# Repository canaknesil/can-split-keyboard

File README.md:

# Can Split Keyboard

Note: THIS KEYBOARD IS NOT READY FOR MANUFACTURING !!!

PCB design for split ortholinear keyboard with 7x6 keys on both sides. 

Can Split Keyboard is based on [Split
Infinitive](https://github.com/peej/for-split-keyboard).

The main differences are
* 7x6 keys on both sides (rather than 6x5) to enable a more complete
  key set. 
* Arduino Nano (rather than Pro Micro).

Inherited features:
* Designed to be easy to build with minimal soldering experience.
* Switch plate cutouts in the PCB so the same PCB can also be used as a switch plate.
* Serial communication over a TRRS cable in split configuration.
* Single PCB design for both keyboard sides.

## Bill of Materials (BOM)

* 4 PCBs, 2 for components and 2 as switch plates.
* 84 MX compatible switches.
* 84 1n4148 diodes.
* 2 Arduino Nano controllers with headers or DIP sockets.
* 2 PJ320A 3.5mm TRRS jacks.
* TRRS cable and micro USB cable.
* 84 MX compatible key caps.

### Tools

* Hacksaw blade or similar
* Flat edged file or sanding paper
* Soldering iron and solder

When uploading the gerber files to the manufacturer, use the default
PCB settings. The plate PCB thickness should be 1.6mm for the switches
to snap into the plate securely. 

## Construction

* You will need 4 PCBs.
* Use a hacksaw blade to remove the cutouts for the switch plate PCBs.
* Solder the diodes onto the underside of each PCB.
* Solder on the Arduino Nano headers (or DIP socket) onto the
  underside of each PCB, do not solder on the Arduino Nano yet.
* Solder the PJ320A TRRS sockets onto the underside of each PCB.
  * There are 2 positions per board, use the right position on the left hand PCB and the left position on the right hand PCB.
  * Ensure that the pins will not foul the placement of the switches and still allow the switches to sit flat on the PCB.
  * You may need to slightly bend the pins inwards away from the switch footprint.
* Insert the switches into the plate and then into the top of the PCBs.
  * Insert all the switches and ensure that the pins of each switch are correctly coming through the board and are not bent under the PCB.
* Solder all the switch pins.
* Solder on the Arduino Nano, ensure that you get them the correct way around, the chip side should be face down towards the PCB.
* Connect the halves together with the TRRS cable.
* Flash both Arduino Nanos with the firmware, see the [QMK documentation](http://qmk.fm/) on how to build and flash the firmware.

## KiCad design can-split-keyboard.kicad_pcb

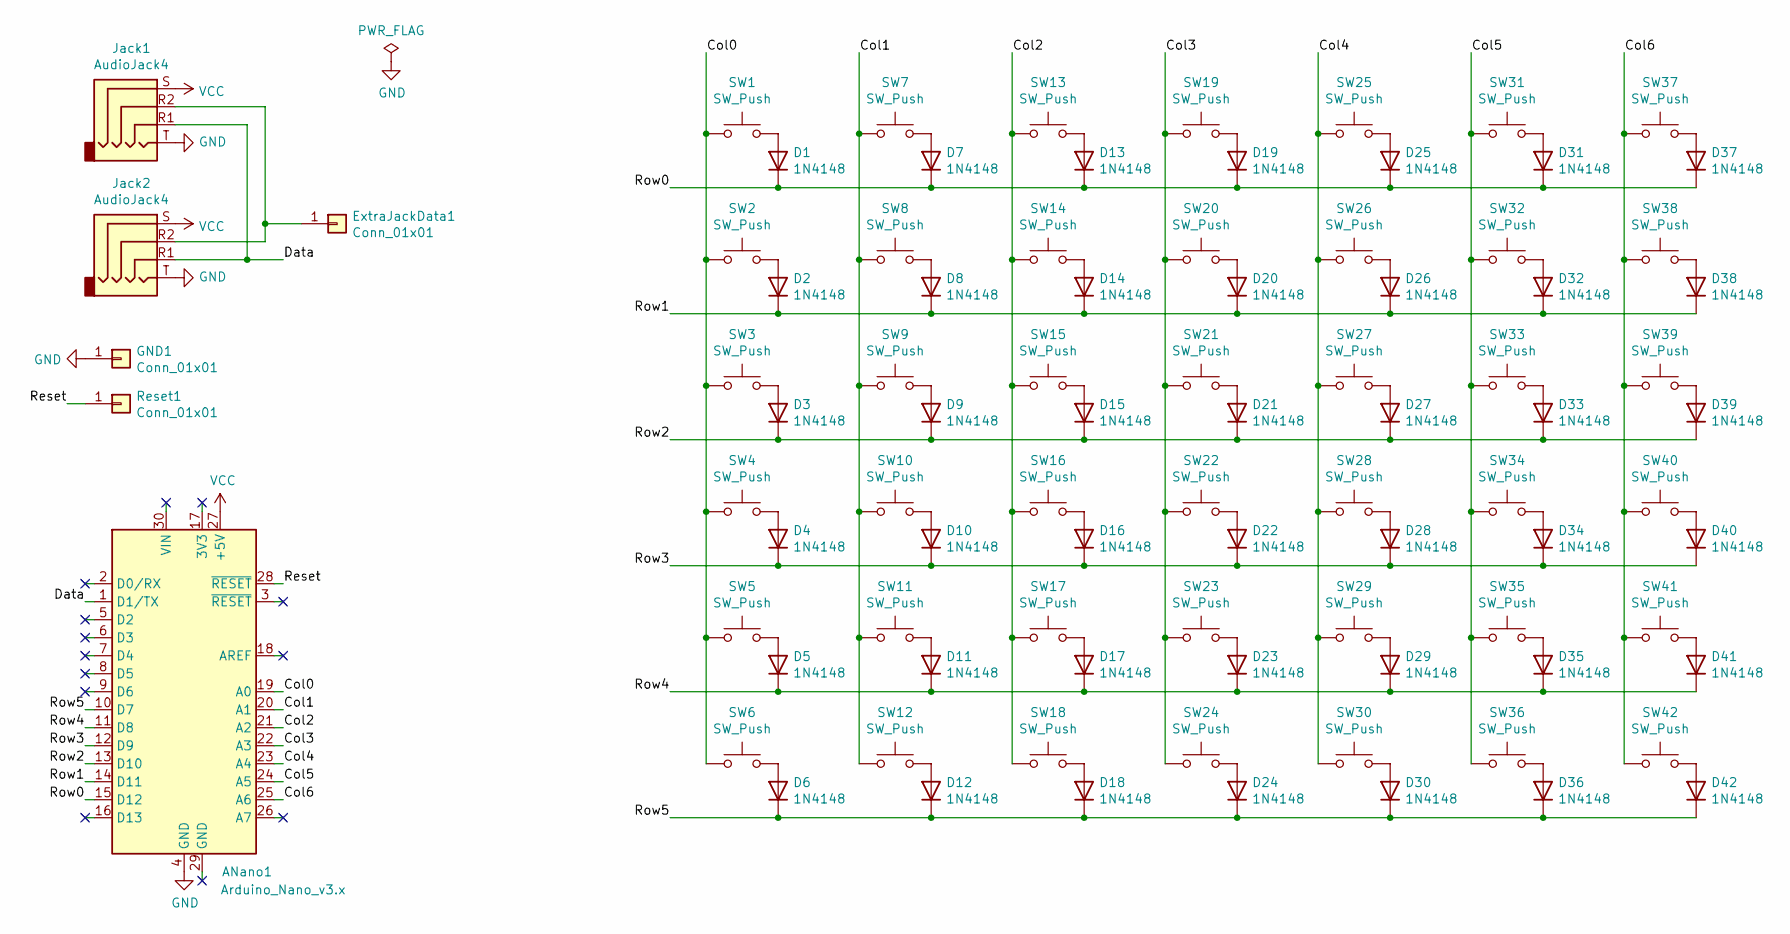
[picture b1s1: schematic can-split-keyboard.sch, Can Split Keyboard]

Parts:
ANano1: Arduino_Nano_v3.x; Arduino_Nano
D1, D2, D3, D4, D5, D6, D7, D8, D9, D10, D11, D12, D13, D14, D15, D16, D17, D18, D19, D20, D21, D22, D23, D24, D25, D26, D27, D28, D29, D30, D31, D32, D33, D34, D35, D36, D37, D38, D39, D40, D41, D42: 1N4148; D_DO-35_SOD27_P7.62mm_Horizontal
ExtraJackData1: Conn_01x01; Single_Pad
GND1: Conn_01x01; Square_Pad
Jack1, Jack2: AudioJack4; PJ-320A
Reset1: Conn_01x01; Square_Pad
SW1, SW2, SW3, SW4, SW5, SW7, SW8, SW9, SW10, SW11, SW13, SW14, SW15, SW16, SW17, SW18, SW19, SW20, SW21, SW22, SW23, SW24, SW25, SW26, SW27, SW28, SW29, SW30, SW31, SW32, SW33, SW34, SW35, SW37, SW38, SW39, SW40, SW41: SW_Push; MX_CUTOUT
SW6, SW36: SW_Push; MX2U_CUTOUT
SW12, SW42: SW_Push; MX

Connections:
/Col0: ANano1.19 (A0), SW1.1, SW2.1, SW3.1, SW4.1, SW5.1, SW6.1
/Col1: ANano1.20 (A1), SW7.1, SW8.1, SW9.1, SW10.1, SW11.1, SW12.1
/Col2: ANano1.21 (A2), SW13.1, SW14.1, SW15.1, SW16.1, SW17.1, SW18.1
/Col3: ANano1.22 (A3), SW19.1, SW20.1, SW21.1, SW22.1, SW23.1, SW24.1
/Col4: ANano1.23 (A4), SW25.1, SW26.1, SW27.1, SW28.1, SW29.1, SW30.1
/Col5: ANano1.24 (A5), SW31.1, SW32.1, SW33.1, SW34.1, SW35.1, SW36.1
/Col6: ANano1.25 (A6), SW37.1, SW38.1, SW39.1, SW40.1, SW41.1, SW42.1
/Data: ANano1.1 (D1/TX), Jack1.R1, Jack2.R1
/Reset: ANano1.28 (~RESET), Reset1.1
/Row0: ANano1.15 (D12), D1.1 (K), D7.1 (K), D13.1 (K), D19.1 (K), D25.1 (K), D31.1 (K), D37.1 (K)
/Row1: ANano1.14 (D11), D2.1 (K), D8.1 (K), D14.1 (K), D20.1 (K), D26.1 (K), D32.1 (K), D38.1 (K)
/Row2: ANano1.13 (D10), D3.1 (K), D9.1 (K), D15.1 (K), D21.1 (K), D27.1 (K), D33.1 (K), D39.1 (K)
/Row3: ANano1.12 (D9), D4.1 (K), D10.1 (K), D16.1 (K), D22.1 (K), D28.1 (K), D34.1 (K), D40.1 (K)
/Row4: ANano1.11 (D8), D5.1 (K), D11.1 (K), D17.1 (K), D23.1 (K), D29.1 (K), D35.1 (K), D41.1 (K)
/Row5: ANano1.10 (D7), D6.1 (K), D12.1 (K), D18.1 (K), D24.1 (K), D30.1 (K), D36.1 (K), D42.1 (K)
GND: ANano1.4 (GND), GND1.1, Jack1.T, Jack2.T
unnamed: D1.2 (A), SW1.2
unnamed: D2.2 (A), SW2.2
unnamed: D3.2 (A), SW3.2
unnamed: D4.2 (A), SW4.2
unnamed: D5.2 (A), SW5.2
unnamed: D6.2 (A), SW6.2
unnamed: D7.2 (A), SW7.2
unnamed: D8.2 (A), SW8.2
unnamed: D9.2 (A), SW9.2
unnamed: D10.2 (A), SW10.2
unnamed: D11.2 (A), SW11.2
unnamed: D12.2 (A), SW12.2
unnamed: D13.2 (A), SW13.2
unnamed: D14.2 (A), SW14.2
unnamed: D15.2 (A), SW15.2
unnamed: D16.2 (A), SW16.2
unnamed: D17.2 (A), SW17.2
unnamed: D18.2 (A), SW18.2
unnamed: D19.2 (A), SW19.2
unnamed: D20.2 (A), SW20.2
unnamed: D21.2 (A), SW21.2
unnamed: D22.2 (A), SW22.2
unnamed: D23.2 (A), SW23.2
unnamed: D24.2 (A), SW24.2
unnamed: D25.2 (A), SW25.2
unnamed: D26.2 (A), SW26.2
unnamed: D27.2 (A), SW27.2
unnamed: D28.2 (A), SW28.2
unnamed: D29.2 (A), SW29.2
unnamed: D30.2 (A), SW30.2
unnamed: D31.2 (A), SW31.2
unnamed: D32.2 (A), SW32.2
unnamed: D33.2 (A), SW33.2
unnamed: D34.2 (A), SW34.2
unnamed: D35.2 (A), SW35.2
unnamed: D36.2 (A), SW36.2
unnamed: D37.2 (A), SW37.2
unnamed: D38.2 (A), SW38.2
unnamed: D39.2 (A), SW39.2
unnamed: D40.2 (A), SW40.2
unnamed: D41.2 (A), SW41.2
unnamed: D42.2 (A), SW42.2
unnamed: ExtraJackData1.1, Jack1.R2, Jack2.R2
VCC: ANano1.27 (+5V), Jack1.S, Jack2.S

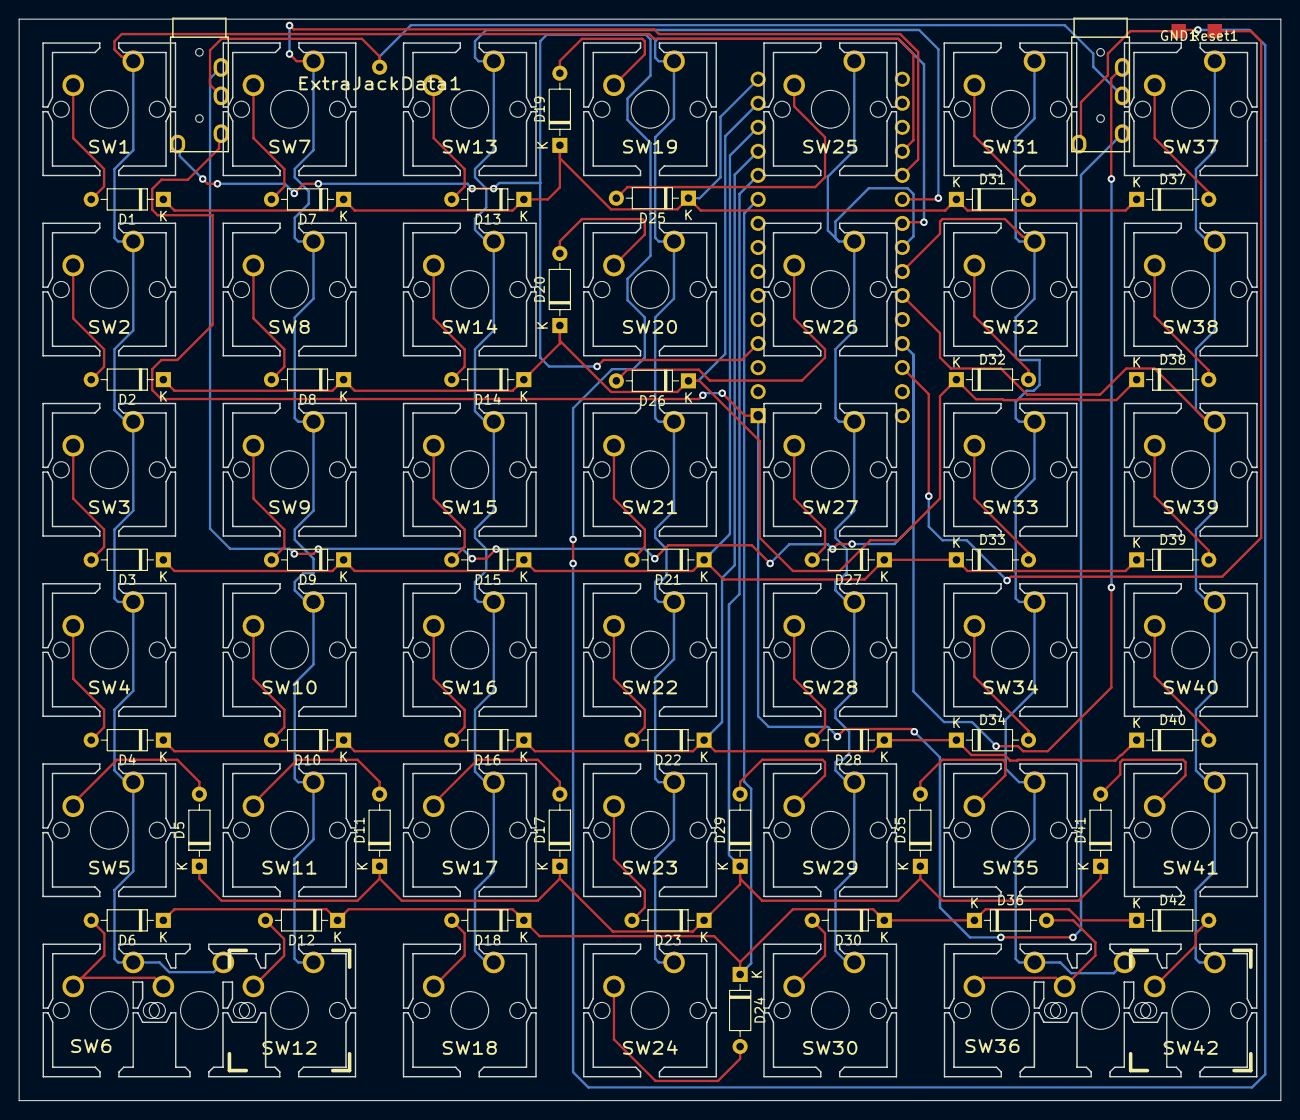
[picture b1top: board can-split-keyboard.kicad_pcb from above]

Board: 2 copper layers, 133.2 x 114.2 mm, 90 parts (1 on the bottom side), 60 nets.

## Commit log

2020-06-28 Created empty project, along with readme and footprints from peej/for-split-keyboard.
2020-06-28 6x7 split keyboard sch with Arduino Nano.
2020-06-28 Added reference to peej footprints from forked repo.
2020-06-28 Assigned footprints to switches.
2020-06-28 Added all the footprints
2020-06-28 Fixed footprints
2020-06-28 Made pins of jack footprint same as in the schematics. Generated the PCB from schematics.
2020-06-28 Placed all the switches on PCB.
2020-06-28 Fixed right buttom corner double key.
2020-06-28 Placed Microcontroller, jacks, and outer edge cut.
2020-06-28 Placed everything.
2020-06-30 Put arduino to the other side of the PCB. Changed track clearence to 0.25mm.
2020-06-30 Placed all the tracks.
2020-07-04 Rewritten README.
